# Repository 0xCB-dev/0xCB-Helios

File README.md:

# 0xCB-Helios

### RP2040 pro micro drop in

|                              Licence                               |                                                      OSHWA                                                       |
| :----------------------------------------------------------------: | :--------------------------------------------------------------------------------------------------------------: |
|  |  |

### Official vendors

Purchasing Helios from any vendors listed here directly supports our work. Helios controllers sourced from vendors not listed here and not produced by us will not receive the same level of support and may have varying degrees of quality.

### EU:

Germany: [KeebSupply](https://keeb.supply/products/0xcb-helios)

Germany: [Keycapsss](https://keycapsss.com/keyboard-parts/mcu-controller/257/0xcb-helios-pro-micro/elite-c-compatible-microcontroller-with-rp2040?c=22)

### Worldwide:

UK: [ProtoTypist](https://prototypist.net/products/in-stock-keeb-supply-0xcb-helios)

USA: [Ringer Keys](https://ringerkeys.com/collections/modders-tools/products/0xcb-helios)

Canada: [RNDKBD](https://rndkbd.com/products/0xcb-helios-microcontroller)

#### Flashing

- `qmk clone`
- `cd qmk_firmware`
- To go to bootloader press the reset button longer than 500ms and release. Alternatively you can short the RST pin to GND, as it's wired to the reset button.
- `make 0xcb/helios:default:flash`

### Assembly

The PCBs are assembled at the fab with the production files located in the /kikit/prod/ dir.

### Integration in your own design

We strongly recommend that you take a look at [ebastler's symbol and footprint library for KiCAD](https://github.com/ebastler/marbastlib).
The Helios files are located in the "promicroish" folder with various mounting options to choose from. 
If you need any help integrating Helios into your keyboard PCB, please feel free to contact us.

### PCB

KiCad 7 stable

[Schematic](https://github.com/0xCB-dev/0xcb-Helios/blob/main/rev1.0/helios.pdf)

### Pinout

| GPIO | F1       | F2        | F3       | F4     | F5  | F6   | F7   | F8           | F9            |
| ---- | -------- | --------- | -------- | ------ | --- | ---- | ---- | ------------ | ------------- |
| 0    | SPI0 RX  | UART0 TX  | I2C0 SDA | PWM0 A | SIO | PIO0 | PIO1 |              | USB OVCUR DET |
| 1    | SPI0 CSn | UART0 RX  | I2C0 SCL | PWM0 B | SIO | PIO0 | PIO1 |              | USB VBUS DET  |
| 2    | SPI0 SCK | UART0 CTS | I2C1 SDA | PWM1 A | SIO | PIO0 | PIO1 |              | USB VBUS EN   |
| 3    | SPI0 TX  | UART0 RTS | I2C1 SCL | PWM1 B | SIO | PIO0 | PIO1 |              | USB OVCUR DET |
| 4    | SPI0 RX  | UART1 TX  | I2C0 SDA | PWM2 A | SIO | PIO0 | PIO1 |              | USB VBUS DET  |
| 5    | SPI0 CSn | UART1 RX  | I2C0 SCL | PWM2 B | SIO | PIO0 | PIO1 |              | USB VBUS EN   |
| 6    | SPI0 SCK | UART1 CTS | I2C1 SDA | PWM3 A | SIO | PIO0 | PIO1 |              | USB OVCUR DET |
| 7    | SPI0 TX  | UART1 RTS | I2C1 SCL | PWM3 B | SIO | PIO0 | PIO1 |              | USB VBUS DET  |
| 8    | SPI1 RX  | UART1 TX  | I2C0 SDA | PWM4 A | SIO | PIO0 | PIO1 |              | USB VBUS EN   |
| 9    | SPI1 CSn | UART1 RX  | I2C0 SCL | PWM4 B | SIO | PIO0 | PIO1 |              | USB OVCUR DET |
| 10   | SPI1 SCK | UART1 CTS | I2C1 SDA | PWM5 A | SIO | PIO0 | PIO1 |              | USB VBUS DET  |
| 11   | SPI1 TX  | UART1 RTS | I2C1 SCL | PWM5 B | SIO | PIO0 | PIO1 |              | USB VBUS EN   |
| 12   | SPI1 RX  | UART0 TX  | I2C0 SDA | PWM6 A | SIO | PIO0 | PIO1 |              | USB OVCUR DET |
| 13   | SPI1 CSn | UART0 RX  | I2C0 SCL | PWM6 B | SIO | PIO0 | PIO1 |              | USB VBUS DET  |
| 14   | SPI1 SCK | UART0 CTS | I2C1 SDA | PWM7 A | SIO | PIO0 | PIO1 |              | USB VBUS EN   |
| 15   | SPI1 TX  | UART0 RTS | I2C1 SCL | PWM7 B | SIO | PIO0 | PIO1 |              | USB OVCUR DET |
| 16   | SPI0 RX  | UART0 TX  | I2C0 SDA | PWM0 A | SIO | PIO0 | PIO1 |              | USB VBUS DET  |
| 17   | SPI0 CSn | UART0 RX  | I2C0 SCL | PWM0 B | SIO | PIO0 | PIO1 |              | USB VBUS EN   |
| 18   | SPI0 SCK | UART0 CTS | I2C1 SDA | PWM1 A | SIO | PIO0 | PIO1 |              | USB OVCUR DET |
| 19   | SPI0 TX  | UART0 RTS | I2C1 SCL | PWM1 B | SIO | PIO0 | PIO1 |              | USB VBUS DET  |
| 20   | SPI0 RX  | UART1 TX  | I2C0 SDA | PWM2 A | SIO | PIO0 | PIO1 | CLOCK GPIN0  | USB VBUS EN   |
| 21   | SPI0 CSn | UART1 RX  | I2C0 SCL | PWM2 B | SIO | PIO0 | PIO1 | CLOCK GPOUT0 | USB OVCUR DET |
| 22   | SPI0 SCK | UART1 CTS | I2C1 SDA | PWM3 A | SIO | PIO0 | PIO1 | CLOCK GPIN1  | USB VBUS DET  |
| 23   | SPI0 TX  | UART1 RTS | I2C1 SCL | PWM3 B | SIO | PIO0 | PIO1 | CLOCK GPOUT1 | USB VBUS EN   |
| 24   | SPI1 RX  | UART1 TX  | I2C0 SDA | PWM4 A | SIO | PIO0 | PIO1 | CLOCK GPOUT2 | USB OVCUR DET |
| 25   | SPI1 CSn | UART1 RX  | I2C0 SCL | PWM4 B | SIO | PIO0 | PIO1 | CLOCK GPOUT3 | USB VBUS DET  |
| 26   | SPI1 SCK | UART1 CTS | I2C1 SDA | PWM5 A | SIO | PIO0 | PIO1 |              | USB VBUS EN   |
| 27   | SPI1 TX  | UART1 RTS | I2C1 SCL | PWM5 B | SIO | PIO0 | PIO1 |              | USB OVCUR DET |
| 28   | SPI1 RX  | UART0 TX  | I2C0 SDA | PWM6 A | SIO | PIO0 | PIO1 |              | USB VBUS DET  |
| 29   | SPI1 CSn | UART0 RX  | I2C0 SCL | PWM6 B | SIO | PIO0 | PIO1 |              | USB VBUS EN   |

#### BOM:

| Comment                 | Designator                             | Footprint                                           | LCSC     |
| ----------------------- | -------------------------------------- | --------------------------------------------------- | -------- |
| 4u7                     | C1                                     | Capacitor_SMD:C_0402_1005Metric                     | C23733   |
| 10u                     | C2,C3,C4,C5                            | Capacitor_SMD:C_0402_1005Metric                     | C15525   |
| 100n                    | C6,C11,C12,C13,C14,C15,C16,C17,C18,C19 | Capacitor_SMD:C_0402_1005Metric                     | C1525    |
| 15p                     | C7,C8                                  | Capacitor_SMD:C_0402_1005Metric                     | C1548    |
| 1u                      | C9,C10                                 | Capacitor_SMD:C_0402_1005Metric                     | C52923   |
| Power LED               | D1                                     | Diode_SMD:D_0402_1005Metric                         | C130719  |
| User LED                | D2                                     | Diode_SMD:D_0402_1005Metric                         | C130724  |
| PMEG2010BELD            | D3                                     | 0xcb:SOD882D                                        | C552820  |
| 500mA                   | F1                                     | Fuse:Fuse_0603_1608Metric                           | C210357  |
| 600R                    | FB1                                    | Resistor_SMD:R_0402_1005Metric                      | C160977  |
| USB_C_Receptacle_USB2.0 | J1                                     | 0xcb:GT-USB-7014C                                   | C963373  |
| 2N7002VC-               | Q1,Q2                                  | Package_TO_SOT_SMD:SOT-563                          | C504145  |
| 10k                     | R1,R2,R3,R11,R17                       | Resistor_SMD:R_0402_1005Metric                      | C25744   |
| 51K                     | R4,R5,R6                               | Resistor_SMD:R_0402_1005Metric                      | C25794   |
| 5k1                     | R7,R8,R16                              | Resistor_SMD:R_0402_1005Metric                      | C25905   |
| 1K                      | R9                                     | Resistor_SMD:R_0402_1005Metric                      | C11702   |
| 1k                      | R10,R14,R15                            | Resistor_SMD:R_0402_1005Metric                      | C11702   |
| 27R                     | R12,R13                                | Resistor_SMD:R_0402_1005Metric                      | C25100   |
| SWITCH                  | SW1                                    | 0xcb:1.9x2.8mm SW                                   | C589221  |
| USBLC6-2P6              | U1                                     | Package_TO_SOT_SMD:SOT-666                          | C2827693 |
| TLV75533PDQNR           | U2                                     | 0xcb:X2SON-4                                        | C2861882 |
| W25Q128JVPIQ            | U3                                     | 0xcb:W25Q128JVPIQ                                   | C190862  |
| RP2040                  | U4                                     | Package_DFN_QFN:QFN-56-1EP_7x7mm_P0.4mm_EP3.2x3.2mm | C2040    |
| 74LVC1T45               | U5                                     | Package_TO_SOT_SMD:SOT-563                          | C352970  |
| 12MHz                   | Y1                                     | Crystal:Crystal_SMD_2520-4Pin_2.5x2.0mm             | C2149204 |

### Credits

The awesome one button reset circuit is based on the one used on the [Sea-picro](https://github.com/joshajohnson/sea-picro) by joshajohnson and this very well written [article](https://acheronproject.com/reset_article_1/reset_article_1/) by the Acheron Project.

Thank you! :heart:

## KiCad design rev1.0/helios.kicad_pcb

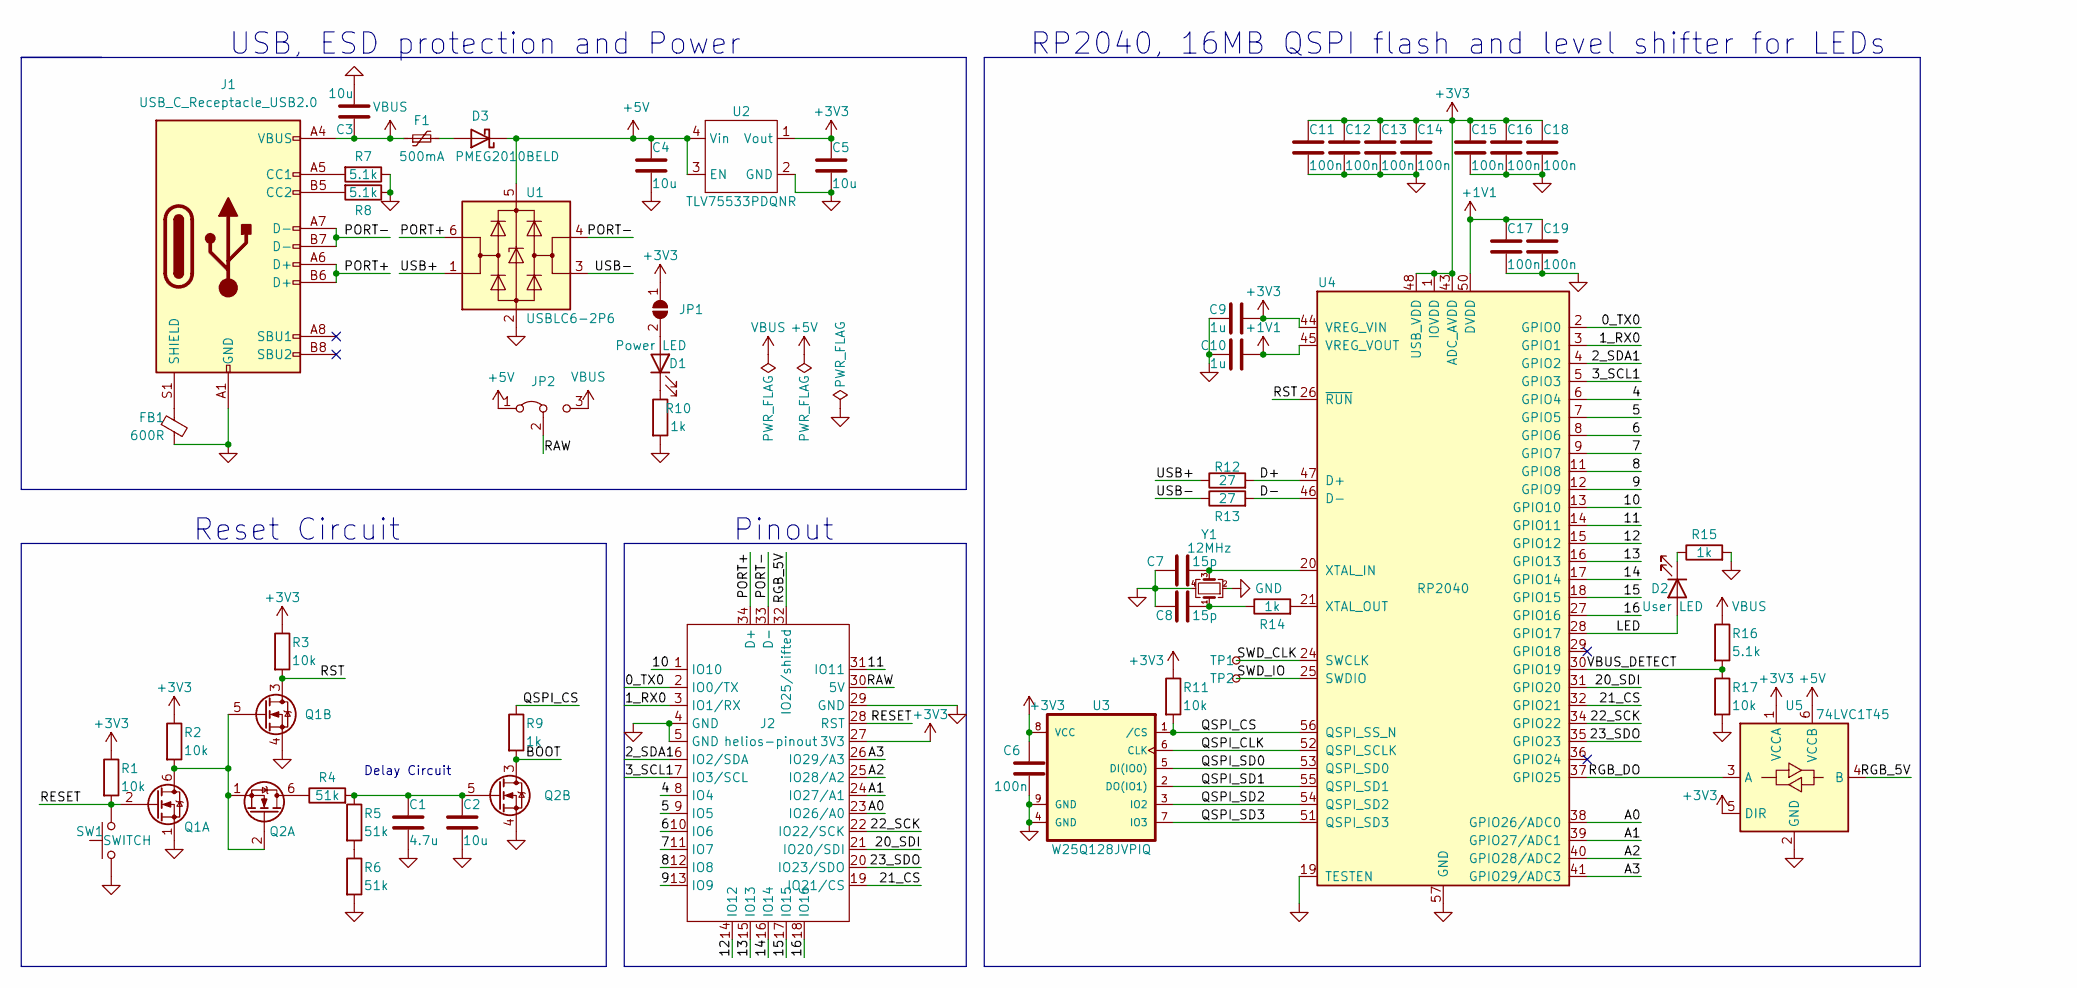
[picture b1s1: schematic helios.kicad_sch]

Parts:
C1: 4.7u; C_0402_1005Metric; MPN 4.7uF 20% 10V 0402; LCSC C23733
C2, C3, C4, C5: 10u; C_0402_1005Metric; MPN 10uF 20% 10V 0402; LCSC C15525
C6, C11, C12, C13, C14, C15, C16, C17, C18, C19: 100n; C_0402_1005Metric; MPN 100nF 10% 10V 0402; LCSC C1525
C7, C8: 15p; C_0402_1005Metric; MPN 15pF 5% 10V; LCSC C1548
C9, C10: 1u; C_0402_1005Metric; MPN 1uF 20% 10V 0402; LCSC C52923
D1: Power LED; D_0402_1005Metric; MPN B1811URO-20D000113U1930; LCSC C130719
D2: User LED; D_0402_1005Metric; MPN B1811NB--05D000113U1930; LCSC C130724
D3: PMEG2010BELD; SOD882D; MPN PMEG2010BELD,315; JLCPCB_CORRECTION 0; 0; 180
F1: 500mA; Fuse_0603_1608Metric; MPN MF-FSMF050X-2; LCSC C210357
FB1: 600R; R_0402_1005Metric; MPN BLM15PX601SN1D; LCSC C160977
J1: USB_C_Receptacle_USB2.0; GT-USB-7014C; MPN USB4510-03-1-A; LCSC C963373
J2: helios-pinout; helios
JP1: SolderJumper_2_Open; SolderJumper-2_P1.3mm_Open_TrianglePad1.0x1.5mm
JP2: Jumper_3_Bridged12; SolderJumper-3_P1.3mm_Bridged12_RoundedPad1.0x1.5mm_NumberL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
Q1, Q2: 2N7002VC-; SOT-563; MPN 2N7002VC; JLCPCB_CORRECTION 0; 0; 180
R1, R2, R3, R11, R17: 10k; R_0402_1005Metric; MPN 10k 1% 0402; LCSC C25744
R4, R5, R6: 51k; R_0402_1005Metric; MPN 51k 1% 0402; LCSC C25794
R7, R8, R16: 5.1k; R_0402_1005Metric; MPN 5.1k 1% 0402; LCSC C25905
R9, R10, R14, R15: 1k; R_0402_1005Metric; MPN 1k 1% 0402; LCSC C11702
R12, R13: 27; R_0402_1005Metric; MPN 27 1% 0402; LCSC C25100
SW1: SWITCH; 1.9x2.8mm SW; MPN EVP-BL2A1B000; LCSC C589221
TP1: CLK; TestPoint_Pad_D0.8mm
TP2: DIO; TestPoint_Pad_D0.8mm
U1: USBLC6-2P6; SOT-666; MPN USBLC6-2P6; JLCPCB_CORRECTION 0; 0; 270
U2: TLV75533PDQNR; X2SON-4; MPN TLV75533PDQNR; LCSC C2861882
U3: W25Q128JVPIQ; MPN W25Q128JVPIQ; JLCPCB_CORRECTION 0; 0; 270
U4: RP2040; QFN-56-1EP_7x7mm_P0.4mm_EP3.2x3.2mm; MPN SC0914(13); LCSC C2040
U5: 74LVC1T45; SOT-563; MPN SN74LVC1T45DRLR; JLCPCB_CORRECTION 0; 0; 270
Y1: 12MHz; Crystal_SMD_2520-4Pin_2.5x2.0mm; MPN ECS-120-10-36B-CWY-TR3; LCSC C2149204

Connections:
+1V1: C10.2, C17.1, C19.1, U4.23 (DVDD), U4.45 (VREG_VOUT), U4.50 (DVDD)
+3V3: C5.1, C6.1, C9.2, C11.1, C12.1, C13.1, C14.1, C15.1, C16.1, C18.1, J2.27 (3V3), JP1.1 (A), R1.1, R2.1, R3.1, R11.1, U2.1 (Vout), U3.8 (VCC), U4.1 (IOVDD), U4.10 (IOVDD), U4.22 (IOVDD), U4.33 (IOVDD), U4.42 (IOVDD), U4.43 (ADC_AVDD), U4.44 (VREG_VIN), U4.48 (USB_VDD), U4.49 (IOVDD), U5.1 (VCCA), U5.5 (DIR)
+5V: C4.1, D3.1 (K), JP2.1 (A), U1.5 (VBUS), U2.3 (EN), U2.4 (Vin), U5.6 (VCCB)
/0_TX0: J2.2 (IO0/TX), U4.2 (GPIO0)
/1_RX0: J2.3 (IO1/RX), U4.3 (GPIO1)
/2_SDA1: J2.6 (IO2/SDA), U4.4 (GPIO2)
/3_SCL1: J2.7 (IO3/SCL), U4.5 (GPIO3)
/4: J2.8 (IO4), U4.6 (GPIO4)
/5: J2.9 (IO5), U4.7 (GPIO5)
/6: J2.10 (IO6), U4.8 (GPIO6)
/7: J2.11 (IO7), U4.9 (GPIO7)
/8: J2.12 (IO8), U4.11 (GPIO8)
/9: J2.13 (IO9), U4.12 (GPIO9)
/10: J2.1 (IO10), U4.13 (GPIO10)
/11: J2.31 (IO11), U4.14 (GPIO11)
/12: J2.14 (IO12), U4.15 (GPIO12)
/13: J2.15 (IO13), U4.16 (GPIO13)
/14: J2.16 (IO14), U4.17 (GPIO14)
/15: J2.17 (IO15), U4.18 (GPIO15)
/16: J2.18 (IO16), U4.27 (GPIO16)
/20_SDI: J2.21 (IO20/SDI), U4.31 (GPIO20)
/21_CS: J2.19 (IO21/CS), U4.32 (GPIO21)
/22_SCK: J2.22 (IO22/SCK), U4.34 (GPIO22)
/23_SDO: J2.20 (IO23/SDO), U4.35 (GPIO23)
/A0: J2.23 (IO26/A0), U4.38 (GPIO26/ADC0)
/A1: J2.24 (IO27/A1), U4.39 (GPIO27/ADC1)
/A2: J2.25 (IO28/A2), U4.40 (GPIO28/ADC2)
/A3: J2.26 (IO29/A3), U4.41 (GPIO29/ADC3)
/BOOT: Q2.3 (D), R9.2
/D+: R12.2, U4.47 (D+)
/D-: R13.2, U4.46 (D-)
/LED: D2.2 (A), U4.28 (GPIO17)
/PORT+: J1.A6 (D+), J1.B6 (D+), J2.34 (D+), U1.6 (I/O1)
/PORT-: J1.A7 (D-), J1.B7 (D-), J2.33 (D-), U1.4 (I/O2)
/QSPI_CLK: U3.6 (CLK), U4.52 (QSPI_SCLK)
/QSPI_CS: R9.1, R11.2, U3.1 (/CS), U4.56 (QSPI_SS_N)
/QSPI_SD0: U3.5 (DI(IO0)), U4.53 (QSPI_SD0)
/QSPI_SD1: U3.2 (DO(IO1)), U4.55 (QSPI_SD1)
/QSPI_SD2: U3.3 (IO2), U4.54 (QSPI_SD2)
/QSPI_SD3: U3.7 (IO3), U4.51 (QSPI_SD3)
/RAW: J2.30 (5V), JP2.2 (C)
/RESET: J2.28 (RST), Q1.2 (G), R1.2, SW1.2
/RGB_5V: J2.32 (IO25/shifted), U5.4 (B)
/RGB_DO: U4.37 (GPIO25), U5.3 (A)
/RST: Q1.3 (D), R3.2, U4.26 (~RUN)
/SWD_CLK: TP1.1, U4.24 (SWCLK)
/SWD_IO: TP2.1, U4.25 (SWDIO)
/USB+: R12.1, U1.1 (I/O1)
/USB-: R13.1, U1.3 (I/O2)
/VBUS_DETECT: R16.2, R17.1, U4.30 (GPIO19)
GND: C1.2, C2.2, C3.2, C4.2, C5.2, C6.2, C7.1, C8.1, C9.1, C10.1, C11.2, C12.2, C13.2, C14.2, C15.2, C16.2, C17.2, C18.2, C19.2, FB1.2, J1.A1 (GND), J1.A12 (GND), J1.B1 (GND), J1.B12 (GND), J2.4 (GND), J2.5 (GND), J2.29 (GND), Q1.1 (S), Q1.4 (S), Q2.4 (S), R6.2, R7.1, R8.1, R10.2, R15.2, R17.2, SW1.1, U1.2 (GND), U2.2 (GND), U2.5 (TP), U3.4 (GND), U3.9 (GND), U4.19 (TESTEN), U4.57 (GND), U5.2 (GND), Y1.2, Y1.4
unnamed: C8.2, R14.1, Y1.1
unnamed: D1.2 (A), JP1.2 (B)
unnamed: D1.1 (K), R10.1
unnamed: D2.1 (K), R15.1
unnamed: D3.2 (A), F1.2
unnamed: J1.A5 (CC1), R7.2
unnamed: J1.B5 (CC2), R8.2
unnamed: FB1.1, J1.S1 (SHIELD)
unnamed: Q1.5 (G), Q1.6 (D), Q2.1 (S), Q2.2 (G), R2.2
unnamed: Q2.6 (D), R4.1
unnamed: C1.1, C2.1, Q2.5 (G), R4.2, R5.1
unnamed: R5.2, R6.1
unnamed: C7.2, U4.20 (XTAL_IN), Y1.3
unnamed: R14.2, U4.21 (XTAL_OUT)
VBUS: C3.1, F1.1, J1.A4 (VBUS), J1.A9 (VBUS), J1.B4 (VBUS), J1.B9 (VBUS), JP2.3 (B), R16.1

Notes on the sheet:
Delay Circuit
USB, ESD protection and Power
RP2040, 16MB QSPI flash and level shifter for LEDs
Reset Circuit
Pinout

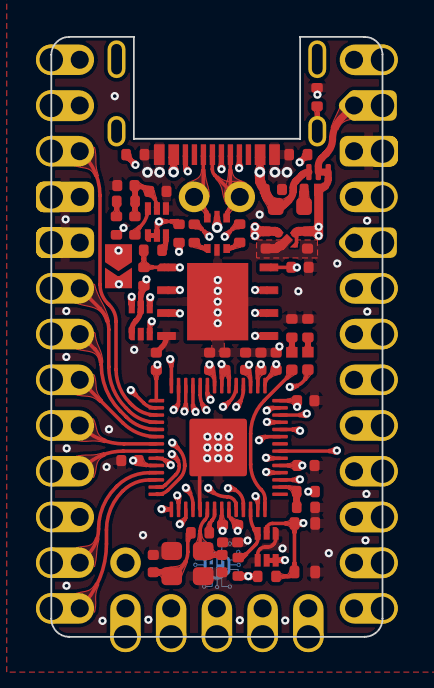
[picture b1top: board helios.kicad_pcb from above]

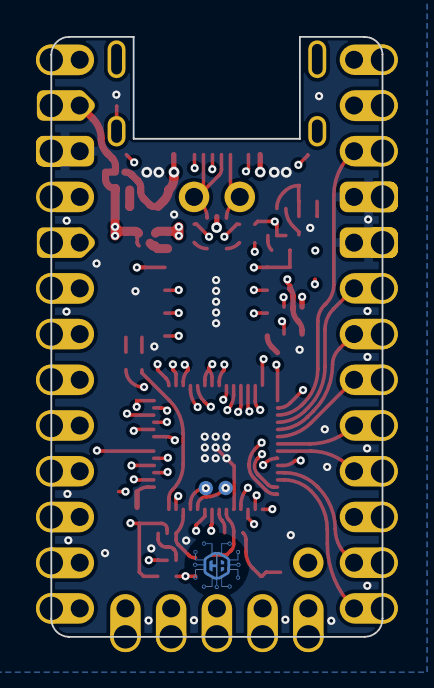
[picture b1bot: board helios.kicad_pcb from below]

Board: 4 copper layers, 18.4 x 33.3 mm, 56 parts (2 on the bottom side), 66 nets.

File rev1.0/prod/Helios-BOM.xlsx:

Comment | Designator | Footprint | JLCPCB Part #（optional） | Substitute | JLC Basic
4u7 | C1 | Capacitor_SMD:C_0402_1005Metric | C23733 | Y | Y
10u | C2, C3, C4, C5 | Capacitor_SMD:C_0402_1005Metric | C15525 | Y | Y
100n | C6, C11, C12, C13, C14, C15, C16, C17, C18, C19 | Capacitor_SMD:C_0402_1005Metric | C1525 | Y | Y
15p | C7, C8 | Capacitor_SMD:C_0402_1005Metric | C1548 | Y | Y
1u | C9, C10 | Capacitor_SMD:C_0402_1005Metric | C52923 | Y | Y
Power LED | D1 | Diode_SMD:D_0402_1005Metric | C130719 | Y | N
User LED | D2 | Diode_SMD:D_0402_1005Metric | C130724 | Y | N
500mA | F1 | Fuse:Fuse_0603_1608Metric | C210357 | Y | N
600R | FB1 | Resistor_SMD:R_0402_1005Metric | C160977 | Y | N
USB_C_Receptacle_USB2.0 | J1 | 0xcb:GT-USB-7014C | C963373 | N | N
2N7002VC- | Q1, Q2 | Package_TO_SOT_SMD:SOT-563 | C504145 | Y | N
10k | R1, R2, R3, R11, R17 | Resistor_SMD:R_0402_1005Metric | C25744 | Y | Y
51K | R4, R5, R6 | Resistor_SMD:R_0402_1005Metric | C25794 | Y | Y
5k1 | R7, R8, R16 | Resistor_SMD:R_0402_1005Metric | C25905 | Y | Y
1K | R9 | Resistor_SMD:R_0402_1005Metric | C11702 | Y | Y
1k | R10, R14, R15 | Resistor_SMD:R_0402_1005Metric | C11702 | Y | Y
27R | R12, R13 | Resistor_SMD:R_0402_1005Metric | C25100 | Y | N
SWITCH | SW1 | 0xcb:1.9x2.8mm SW | C589221 | N | N
USBLC6-2P6 | U1 | Package_TO_SOT_SMD:SOT-666 | C2827693 | N | N
LP5907SNX-3.3-NOPB | U2 | 0xcb:X2SON-4 | C133572 | N | N
W25Q128JVPIQ | U3 | 0xcb:W25Q128JVPIQ | C190862 | N | N
RP2040 | U4 | Package_DFN_QFN:QFN-56-1EP_7x7mm_P0.4mm_EP3.2x3.2mm | C2040 | N | N
74LVC1T45 | U5 | Package_TO_SOT_SMD:SOT-563 | C352970 | N | N
12MHz | Y1 | Crystal:Crystal_SMD_2520-4Pin_2.5x2.0mm | C2149204 | N | N

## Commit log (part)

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2022-09-17 schematic, pcb and BOM done
2022-09-17 production files for ptotos
2022-09-18 added prod files for jlcpcb
2022-09-19 fixed jlc issue
2022-09-20 updated assembly files again
2022-10-12 fixed proto mistakes, revised power circuit and added option to use vbus on the 5v pin
2022-10-20 prod files
2022-12-15 production files
2022-12-28 Readme fixup
2023-01-07 added KiCAD files
2023-03-21 fix helios library
2023-05-29 add castellated holes
2023-06-03 fix tabs in pads
2023-06-04 change over to mouse bites
2023-08-03 widen tabs
2023-08-03 widen tabs even more
2023-08-29 manu change
2023-11-04 Update README.md
    see #4
2023-11-05 Fix readme and add current prod
2023-11-05 Fix typo
